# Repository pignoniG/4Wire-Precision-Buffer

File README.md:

# 4-Wire Precision Buffer

A bipolar, two-channel precision buffer with 4-wire (force/sense) outputs, designed in KiCad 9. I built it to buffer a DC voltage reference (an ADR1399 module) without loading it, and to add remote sense to sources that don't have it, such as the HP 3245A.

## View the design

Open the files in the browser with [KiCanvas](https://kicanvas.org), no KiCad needed:

- [Schematic](https://kicanvas.org/?github=https://github.com/pignoniG/4Wire-Precision-Buffer/blob/main/kicad/4wPrecisionBuffer.kicad_sch)
- [PCB layout](https://kicanvas.org/?github=https://github.com/pignoniG/4Wire-Precision-Buffer/blob/main/kicad/4wPrecisionBuffer.kicad_pcb)

## How it works

Each channel is a composite amplifier:

- an **ADA4523** chopper op amp sets the DC accuracy;
- a **BUF634A** inside its loop supplies the output current;
- at DC, feedback comes from the **sense** terminal, so lead resistance doesn't matter. At higher frequencies, feedback comes from the BUF634A output through a capacitor, for stability;
- a small resistor isolates the BUF634A from the force terminal, and 200 kΩ from force to sense keeps the output defined if the sense leads are open;
- an RC filter protects each input.

One channel follows the HI input and the other the LO input, so the input floats with respect to the ±15 V supply.

The layout is aimed at keeping thermoelectric EMF and leakage low:

- identical, translated channels;
- high-impedance nodes on the top layer with no vias;
- slots and a split ground pour between the warm parts and the inputs;
- bare-copper (OSP) pads for copper ring lugs.

## Repository

- `kicad/`: KiCad project (schematic and PCB).
- `fabrication/gerbers/`: Gerber and drill files for the v6 board.

## Status

The v6 board is built and working. The PCB file carries the current component values; some values in the schematic are older. Characterisation (offset, noise, load regulation, stability) is in progress.

## Licence

MIT, see [LICENSE](LICENSE).

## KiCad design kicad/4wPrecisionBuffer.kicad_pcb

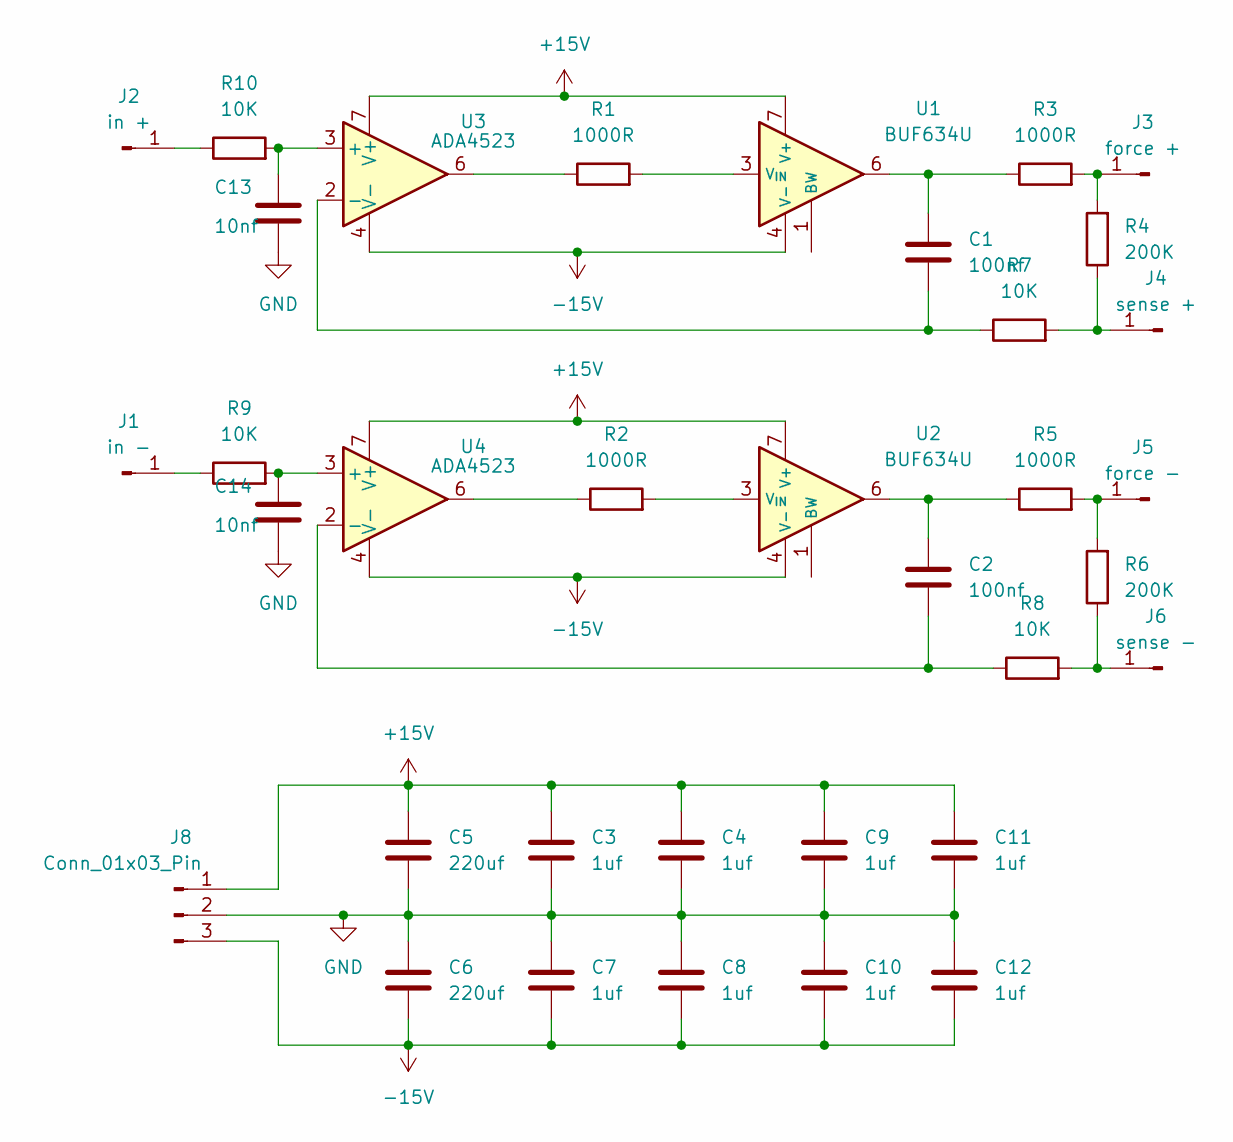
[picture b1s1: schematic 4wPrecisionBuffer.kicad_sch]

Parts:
C1, C2: 100nf; C_1206_3216Metric_Pad1.33x1.80mm_HandSolder
C3, C4, C7, C8, C9, C10, C11, C12: 1uf; C_1206_3216Metric_Pad1.33x1.80mm_HandSolder
C5, C6: 220uf; CP_Elec_10x10.5
C13, C14: 10nf; C_1206_3216Metric_Pad1.33x1.80mm_HandSolder
J1: in -; MountingHole_4.3mm_M4_Pad_TopBottom
J2: in +; MountingHole_4.3mm_M4_Pad_TopBottom
J3: force +; MountingHole_4.3mm_M4_Pad_TopBottom
J4: sense +; MountingHole_4.3mm_M4_Pad_TopBottom
J5: force -; MountingHole_4.3mm_M4_Pad_TopBottom
J6: sense -; MountingHole_4.3mm_M4_Pad_TopBottom
J8: Conn_01x03_Pin; SolderWire-0.15sqmm_1x03_P4mm_D0.5mm_OD1.5mm
R1, R2, R3, R5: 1000R; R_1206_3216Metric_Pad1.30x1.75mm_HandSolder
R4, R6: 200K; R_1206_3216Metric_Pad1.30x1.75mm_HandSolder
R7, R8, R9, R10: 10K; R_1206_3216Metric_Pad1.30x1.75mm_HandSolder
U1, U2: BUF634U; SOIC-8_3.9x4.9mm_P1.27mm
U3, U4: ADA4523; SOIC-8_3.9x4.9mm_P1.27mm

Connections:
+15V: C3.1, C4.1, C5.1, C9.1, C11.1, J8.1, U1.7 (V+), U2.7 (V+), U3.7 (V+), U4.7 (V+)
-15V: C6.2, C7.2, C8.2, C10.2, C12.2, J8.3, U1.4 (V-), U2.4 (V-), U3.4 (V-), U4.4 (V-)
GND: C3.2, C4.2, C5.2, C6.1, C7.1, C8.1, C9.2, C10.1, C11.2, C12.1, C13.2, C14.2, J8.2
unnamed: C1.1, R3.1, U1.6
unnamed: C2.1, R5.1, U2.6
unnamed: J1.1, R9.1
unnamed: J2.1, R10.1
unnamed: J3.1, R3.2, R4.2
unnamed: J4.1, R4.1, R7.2
unnamed: J5.1, R5.2, R6.2
unnamed: J6.1, R6.1, R8.2
unnamed: R1.1, U3.6
unnamed: R2.1, U4.6
unnamed: R1.2, U1.3 (V_{IN})
unnamed: R2.2, U2.3 (V_{IN})
unnamed: C13.1, R10.2, U3.3 (+)
unnamed: C1.2, R7.1, U3.2 (-)
unnamed: C14.1, R9.2, U4.3 (+)
unnamed: C2.2, R8.1, U4.2 (-)

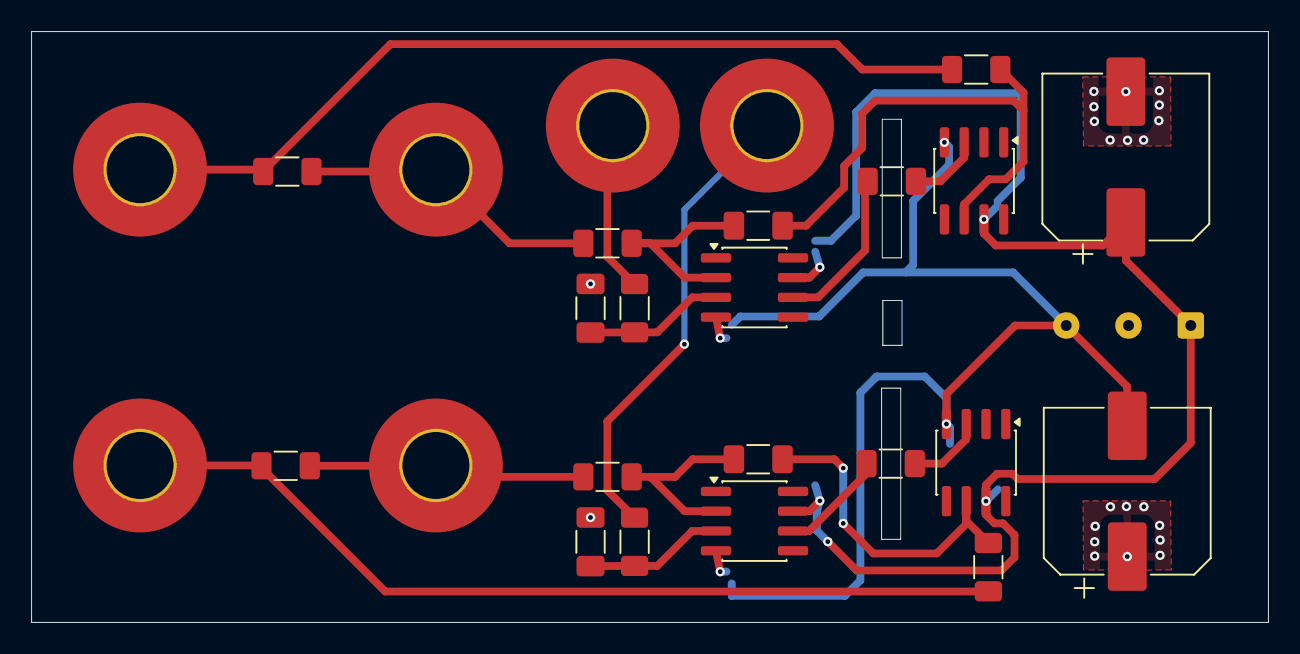
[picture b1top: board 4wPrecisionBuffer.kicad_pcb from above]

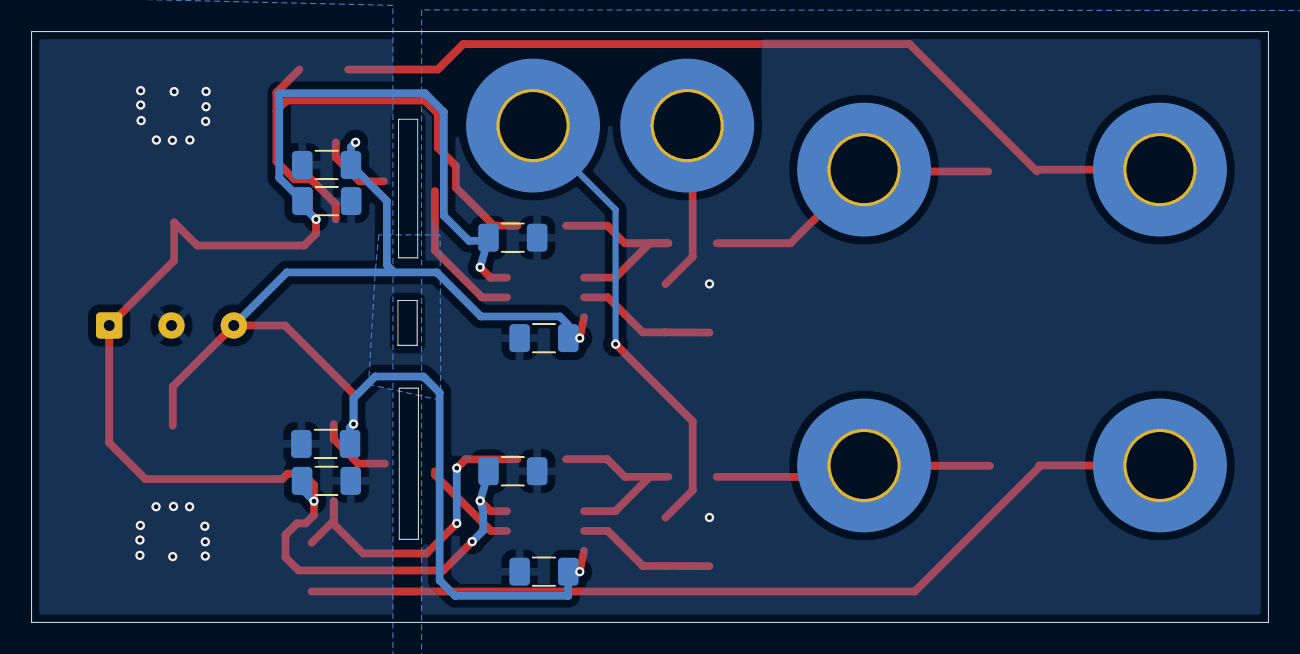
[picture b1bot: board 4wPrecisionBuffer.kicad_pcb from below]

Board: 2 copper layers, 79.4 x 38.0 mm, 35 parts (8 on the bottom side), 19 nets.
